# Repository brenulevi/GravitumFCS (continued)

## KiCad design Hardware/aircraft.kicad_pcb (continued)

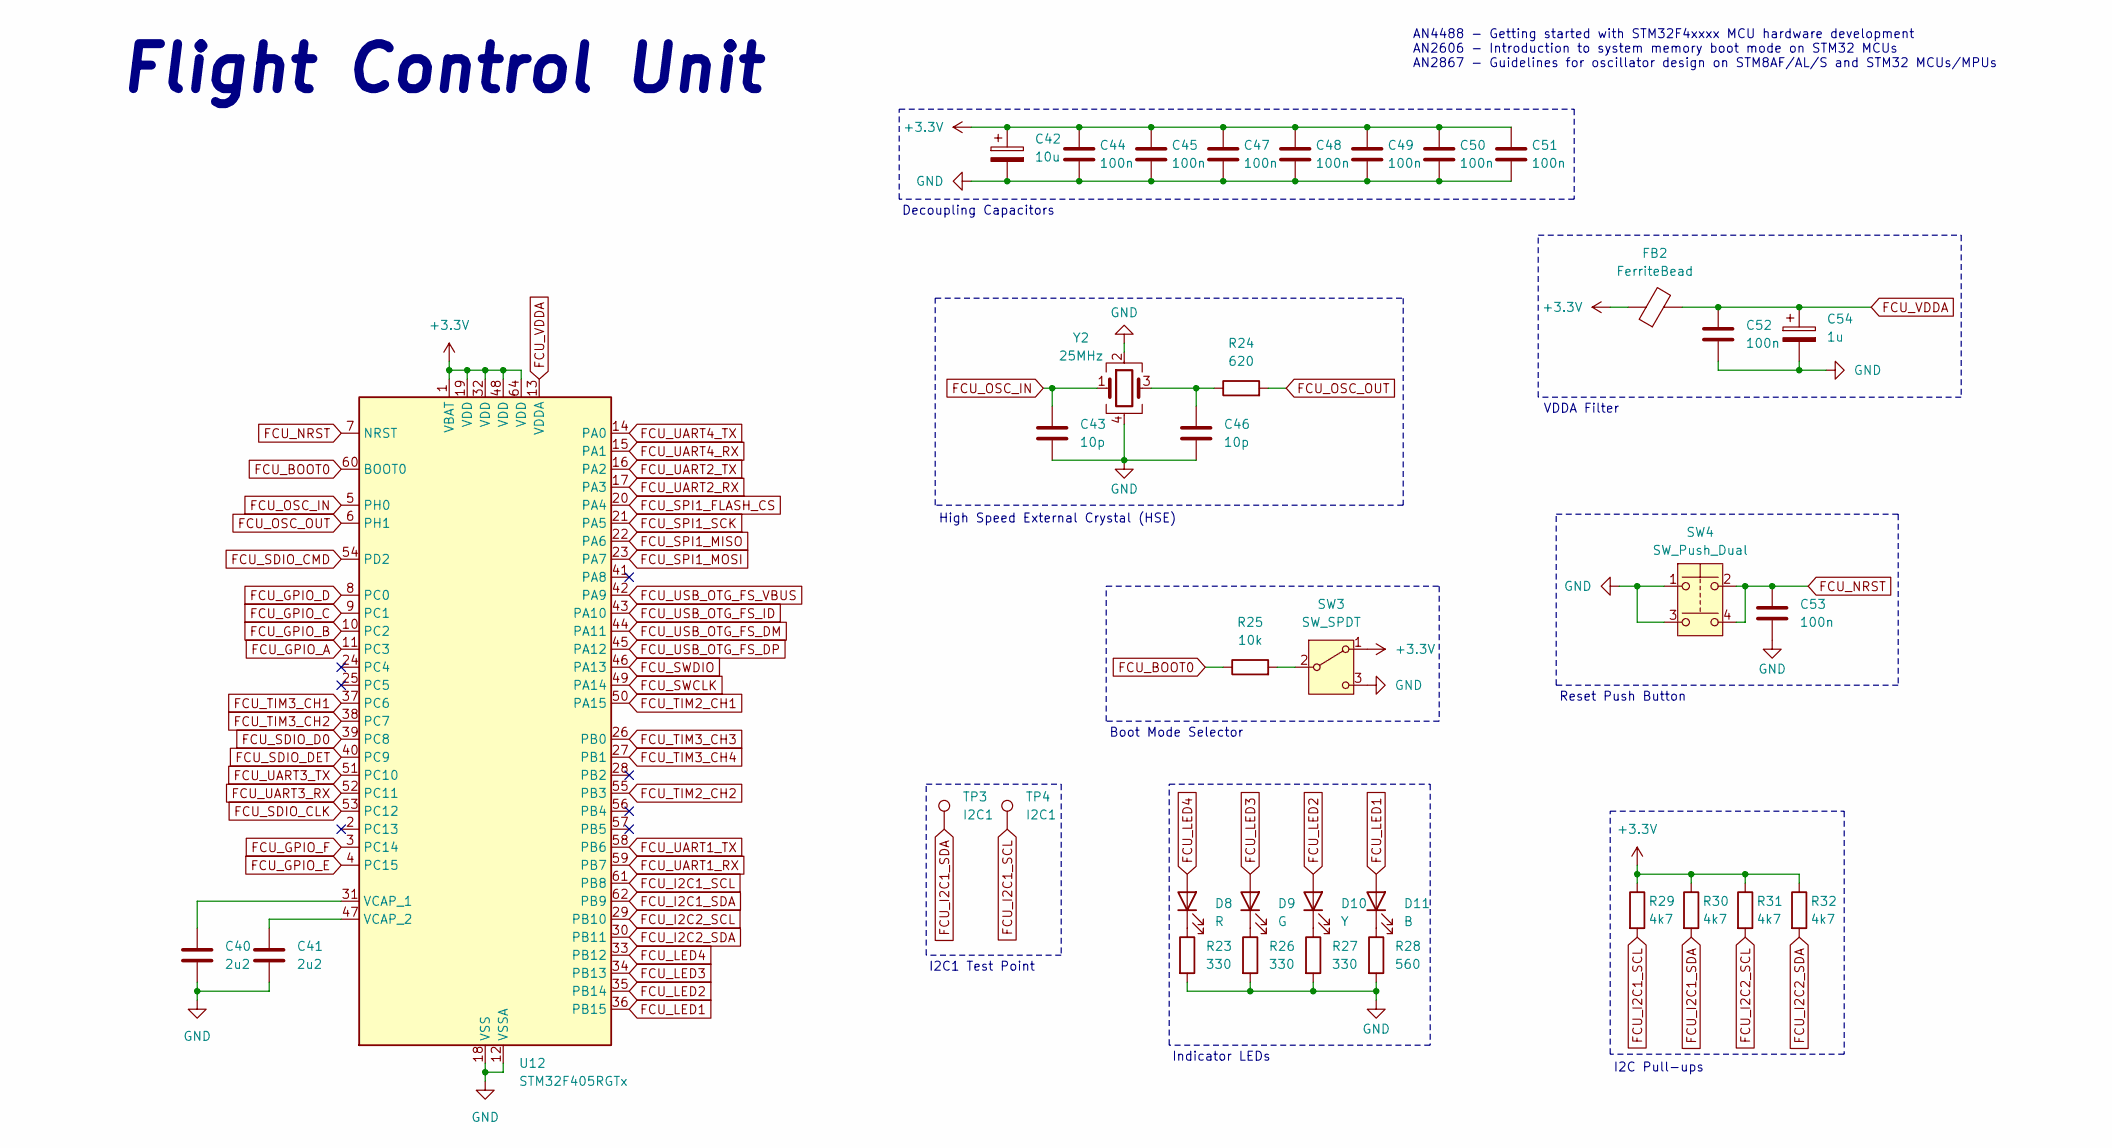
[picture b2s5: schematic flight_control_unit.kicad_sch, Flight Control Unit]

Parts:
C40, C41: 2u2; C_0402_1005Metric; MPN CL10B225KP8NNNC
C42: 10u; C_0603_1608Metric; MPN TAJA106K010TNJ
C43, C46: 10p; C_0402_1005Metric; MPN 885012005007
C44, C45, C47, C48, C49, C50, C51, C52: 100n; C_0402_1005Metric; MPN CL05B104KP5NNNC
C53: 100n; C_0402_1005Metric; MPN C0603C104K8RACTU
C54: 1u; CP_EIA-1608-08_AVX-J; MPN T491A105K010AT
D8: R; LED_0402_1005Metric; MPN LTST-C171KRKT
D9: G; LED_0402_1005Metric; MPN LTST-C170GKT
D10: Y; LED_0402_1005Metric; MPN LTST-C171YKT
D11: B; LED_0402_1005Metric; MPN LTST-C171TBKT
FB2: FerriteBead; L_0402_1005Metric; MPN HZ0805E601R-10
R23, R26, R27: 330; R_0402_1005Metric; MPN RC0603JR-07330RL
R24: 620; R_0402_1005Metric; MPN RC0603FR-07620RL
R25: 10k; R_0402_1005Metric; MPN RC0603FR-0710KL
R28: 560; R_0402_1005Metric; MPN RMCF0603FT560R
R29, R30, R31, R32: 4k7; R_0402_1005Metric; MPN ERJ-3EKF4701V
SW3: SW_SPDT; SW_SPDT_PCM12; MPN PCM12SMTR
SW4: SW_Push_Dual; SW4_PTS815 SJM 250 SMTR LFS_CNK; MPN PTS815SJM250SMTRLFS
TP3, TP4: I2C1; TestPoint_Pad_D1.0mm
U12: STM32F405RGTx; LQFP-64_10x10mm_P0.5mm; MPN STM32F405RGT6
Y2: 25MHz; Crystal_SMD_Abracon_ABM8G-4Pin_3.2x2.5mm; MPN ABM8G-25.000MHZ-B4Y-T3

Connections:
+3.3V: C42.1, C44.1, C45.1, C47.1, C48.1, C49.1, C50.1, C51.1, FB2.1, R29.1, R30.1, R31.1, R32.1, SW3.1 (A), U12.1 (VBAT), U12.19 (VDD), U12.32 (VDD), U12.48 (VDD), U12.64 (VDD); also elsewhere on the board
FCU_BOOT0: R25.1, U12.60 (BOOT0)
FCU_GPIO_A: U12.11 (PC3); also elsewhere on the board
FCU_GPIO_B: U12.10 (PC2); also elsewhere on the board
FCU_GPIO_C: U12.9 (PC1); also elsewhere on the board
FCU_GPIO_D: U12.8 (PC0); also elsewhere on the board
FCU_GPIO_E: U12.4 (PC15); also elsewhere on the board
FCU_GPIO_F: U12.3 (PC14); also elsewhere on the board
FCU_I2C1_SCL: R29.2, TP4.1, U12.61 (PB8); also elsewhere on the board
FCU_I2C1_SDA: R30.2, TP3.1, U12.62 (PB9); also elsewhere on the board
FCU_I2C2_SCL: R31.2, U12.29 (PB10); also elsewhere on the board
FCU_I2C2_SDA: R32.2, U12.30 (PB11); also elsewhere on the board
FCU_LED1: D11.2 (A), U12.36 (PB15)
FCU_LED2: D10.2 (A), U12.35 (PB14)
FCU_LED3: D9.2 (A), U12.34 (PB13)
FCU_LED4: D8.2 (A), U12.33 (PB12)
FCU_NRST: C53.1, SW4.2, SW4.4, U12.7 (NRST); also elsewhere on the board
FCU_OSC_IN: C43.1, U12.5 (PH0), Y2.1
FCU_OSC_OUT: R24.2, U12.6 (PH1)
FCU_SDIO_CLK: U12.53 (PC12); also elsewhere on the board
FCU_SDIO_CMD: U12.54 (PD2); also elsewhere on the board
FCU_SDIO_D0: U12.39 (PC8); also elsewhere on the board
FCU_SDIO_DET: U12.40 (PC9); also elsewhere on the board
FCU_SPI1_FLASH_CS: U12.20 (PA4); also elsewhere on the board
FCU_SPI1_MISO: U12.22 (PA6); also elsewhere on the board
FCU_SPI1_MOSI: U12.23 (PA7); also elsewhere on the board
FCU_SPI1_SCK: U12.21 (PA5); also elsewhere on the board
FCU_SWCLK: U12.49 (PA14); also elsewhere on the board
FCU_SWDIO: U12.46 (PA13); also elsewhere on the board
FCU_TIM2_CH1: U12.50 (PA15); also elsewhere on the board
FCU_TIM2_CH2: U12.55 (PB3); also elsewhere on the board
FCU_TIM3_CH1: U12.37 (PC6); also elsewhere on the board
FCU_TIM3_CH2: U12.38 (PC7); also elsewhere on the board
FCU_TIM3_CH3: U12.26 (PB0); also elsewhere on the board
FCU_TIM3_CH4: U12.27 (PB1); also elsewhere on the board
FCU_UART1_RX: U12.59 (PB7); also elsewhere on the board
FCU_UART1_TX: U12.58 (PB6); also elsewhere on the board
FCU_UART2_RX: U12.17 (PA3); also elsewhere on the board
FCU_UART2_TX: U12.16 (PA2); also elsewhere on the board
FCU_UART3_RX: U12.52 (PC11); also elsewhere on the board
FCU_UART3_TX: U12.51 (PC10); also elsewhere on the board
FCU_UART4_RX: U12.15 (PA1); also elsewhere on the board
FCU_UART4_TX: U12.14 (PA0); also elsewhere on the board
FCU_USB_OTG_FS_ID: U12.43 (PA10); also elsewhere on the board
FCU_USB_OTG_FS_VBUS: U12.42 (PA9); also elsewhere on the board
FCU_VDDA: C52.1, C54.1, FB2.2, U12.13 (VDDA)
GND: C40.2, C41.2, C42.2, C43.2, C44.2, C45.2, C46.2, C47.2, C48.2, C49.2, C50.2, C51.2, C52.2, C53.2, C54.2, R23.2, R26.2, R27.2, R28.2, SW3.3 (C), SW4.1, SW4.3, U12.12 (VSSA), U12.18 (VSS), U12.63 (VSS), Y2.2, Y2.4; also elsewhere on the board
unnamed: C46.1, R24.1, Y2.3
unnamed: D8.1 (K), R23.1
unnamed: D9.1 (K), R26.1
unnamed: D10.1 (K), R27.1
unnamed: D11.1 (K), R28.1
unnamed: R25.2, SW3.2 (B)
unnamed: C40.1, U12.31 (VCAP_1)
unnamed: C41.1, U12.47 (VCAP_2)

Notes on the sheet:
Reset Push Button
VDDA Filter
Decoupling Capacitors
I2C Pull-ups
Flight Control Unit
AN4488 - Getting started with STM32F4xxxx MCU hardware development AN2606 - Introduction to system memory boot mode on STM32 MCUs AN2867 - Guidelines for oscillator design on STM8AF/AL/S and STM32 MCUs/MPUs
Indicator LEDs
Boot Mode Selector
High Speed External Crystal (HSE)
I2C1 Test Point

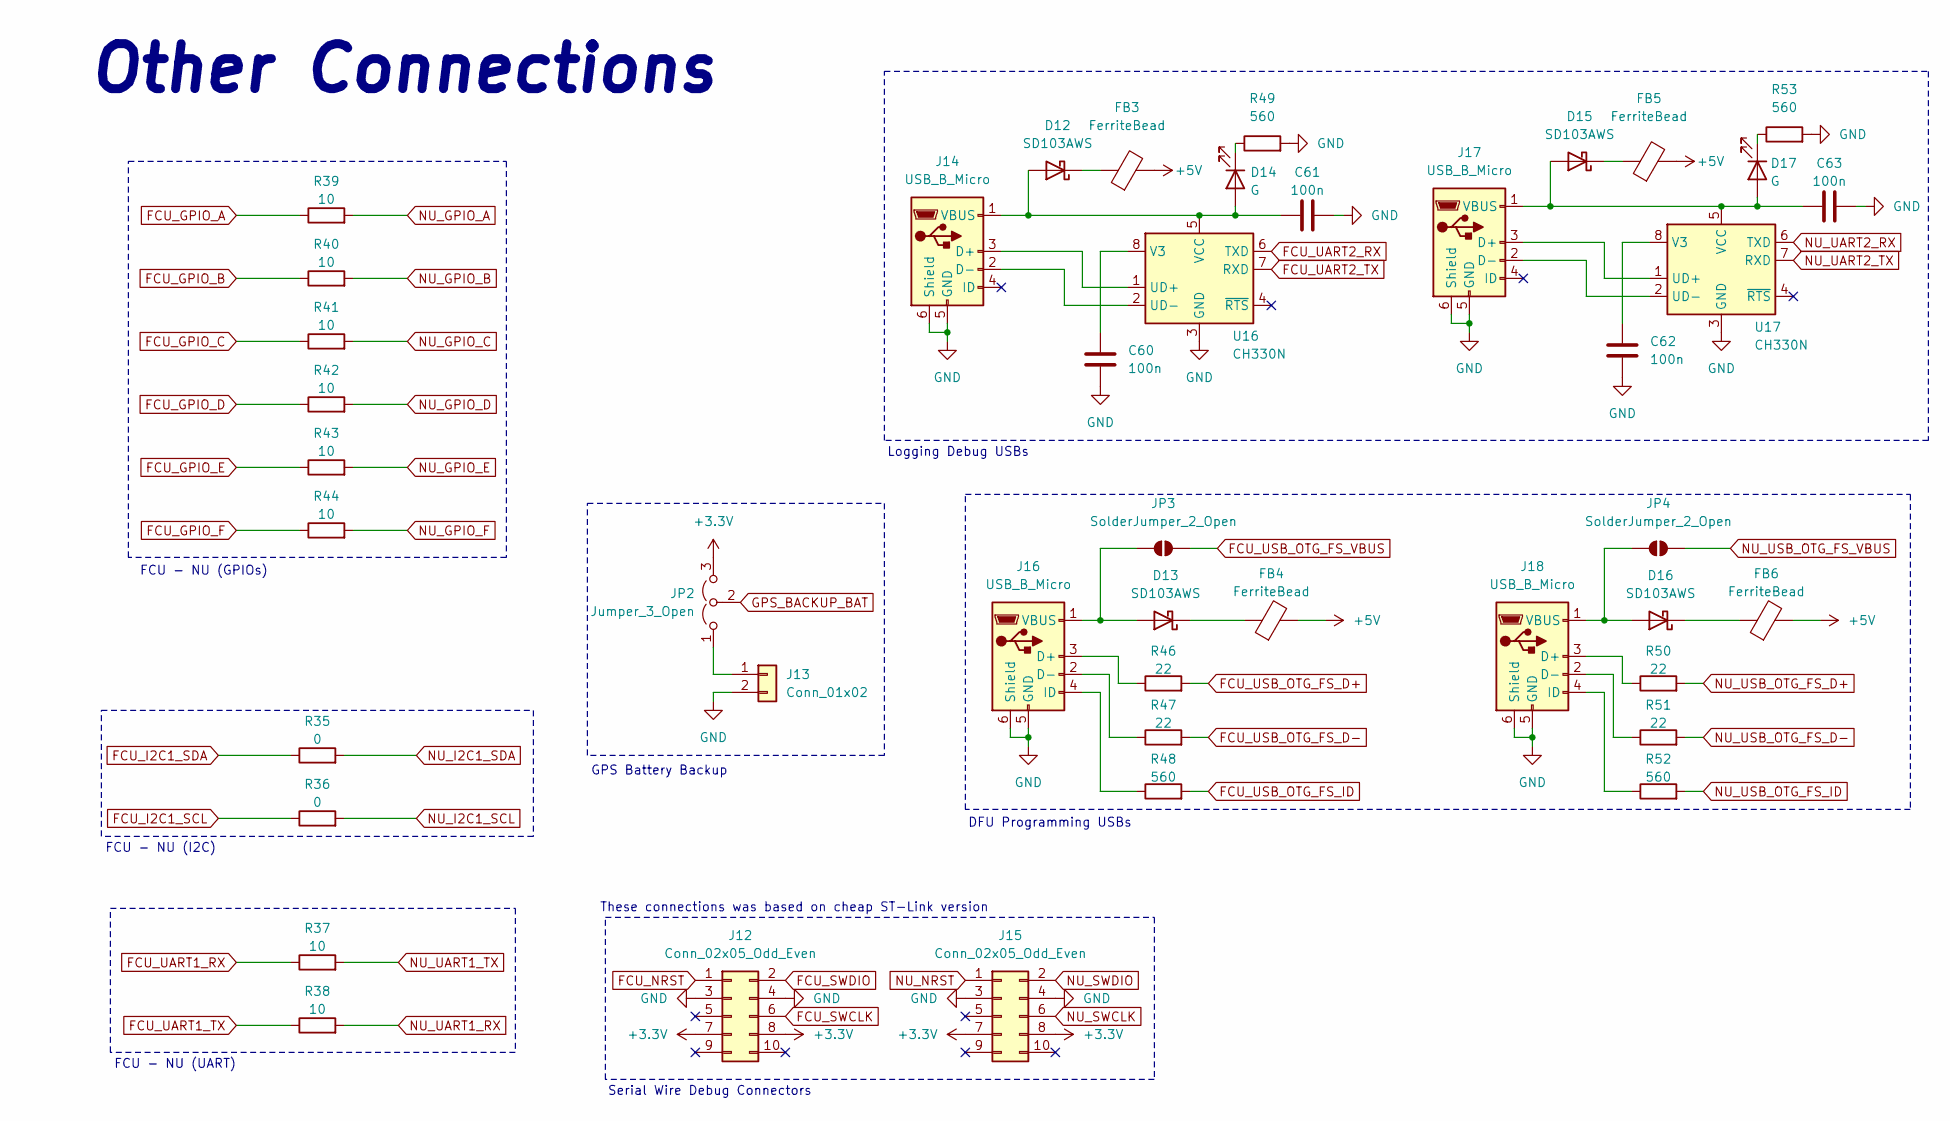
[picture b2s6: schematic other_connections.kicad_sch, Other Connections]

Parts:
C60, C62: 100n; C_0402_1005Metric; MPN C0603C104K8RACTU
C61, C63: 100n; C_0603_1608Metric; MPN C0603C104K8RACTU
D12, D13, D15, D16: SD103AWS; D_SOD-323_HandSoldering; MPN SD103AWS
D14, D17: G; LED_0402_1005Metric; MPN LTST-S270KGKT
FB3, FB4, FB5, FB6: FerriteBead; L_0603_1608Metric; MPN HZ0805E601R-10
J12, J15: Conn_02x05_Odd_Even; JST_PHD_B10B-PHDSS_2x05_P2.00mm_Vertical; MPN B10B-PHDSS
J13: Conn_01x02; JST_PH_S2B-PH-K_1x02_P2.00mm_Horizontal; MPN S2B-PH-K-S
J14, J16, J17, J18: USB_B_Micro; USB_Micro-B_Molex_47346-0001; MPN 0473461001
JP2: Jumper_3_Open; SolderJumper-3_P1.3mm_Open_RoundedPad1.0x1.5mm_NumberLabels
JP3, JP4: SolderJumper_2_Open; SolderJumper-2_P1.3mm_Open_RoundedPad1.0x1.5mm
R35, R36: 0; R_0402_1005Metric; MPN RC0603JR-070RL
R37, R38, R39, R40, R41, R42, R43, R44: 10; R_0402_1005Metric; MPN RMCF0603FT10R0
R46, R47, R50, R51: 22; R_0402_1005Metric; MPN RC0603FR-0722RL
R48, R49, R52, R53: 560; R_0402_1005Metric; MPN RMCF0603FT560R
U16, U17: CH330N; SOIC-8_3.9x4.9mm_P1.27mm; MPN CH330N

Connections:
+3.3V: J12.7, J12.8, J15.7, J15.8, JP2.3 (B); also elsewhere on the board
+5V: FB3.2, FB4.2, FB5.2, FB6.2; also elsewhere on the board
FCU_GPIO_A: R39.1; also elsewhere on the board
FCU_GPIO_B: R40.1; also elsewhere on the board
FCU_GPIO_C: R41.1; also elsewhere on the board
FCU_GPIO_D: R42.1; also elsewhere on the board
FCU_GPIO_E: R43.1; also elsewhere on the board
FCU_GPIO_F: R44.1; also elsewhere on the board
FCU_I2C1_SCL: R36.1; also elsewhere on the board
FCU_I2C1_SDA: R35.1; also elsewhere on the board
FCU_NRST: J12.1; also elsewhere on the board
FCU_SWCLK: J12.6; also elsewhere on the board
FCU_SWDIO: J12.2; also elsewhere on the board
FCU_UART1_RX: R37.1; also elsewhere on the board
FCU_UART1_TX: R38.1; also elsewhere on the board
FCU_UART2_RX: U16.6 (TXD); also elsewhere on the board
FCU_UART2_TX: U16.7 (RXD); also elsewhere on the board
FCU_USB_OTG_FS_ID: R48.2; also elsewhere on the board
FCU_USB_OTG_FS_VBUS: JP3.2 (B); also elsewhere on the board
GND: C60.2, C61.2, C62.2, C63.2, J12.3, J12.4, J13.2, J14.5 (GND), J14.6 (Shield), J15.3, J15.4, J16.5 (GND), J16.6 (Shield), J17.5 (GND), J17.6 (Shield), J18.5 (GND), J18.6 (Shield), R49.2, R53.2, U16.3 (GND), U17.3 (GND); also elsewhere on the board
GPS_BACKUP_BAT: JP2.2 (C); also elsewhere on the board
NU_GPIO_A: R39.2; also elsewhere on the board
NU_GPIO_B: R40.2; also elsewhere on the board
NU_GPIO_C: R41.2; also elsewhere on the board
NU_GPIO_D: R42.2; also elsewhere on the board
NU_GPIO_E: R43.2; also elsewhere on the board
NU_GPIO_F: R44.2; also elsewhere on the board
NU_I2C1_SCL: R36.2; also elsewhere on the board
NU_I2C1_SDA: R35.2; also elsewhere on the board
NU_NRST: J15.1; also elsewhere on the board
NU_SWCLK: J15.6; also elsewhere on the board
NU_SWDIO: J15.2; also elsewhere on the board
NU_UART1_RX: R38.2; also elsewhere on the board
NU_UART1_TX: R37.2; also elsewhere on the board
NU_UART2_RX: U17.6 (TXD); also elsewhere on the board
NU_UART2_TX: U17.7 (RXD); also elsewhere on the board
NU_USB_OTG_FS_D+: R50.2; also elsewhere on the board
NU_USB_OTG_FS_D-: R51.2; also elsewhere on the board
NU_USB_OTG_FS_ID: R52.2; also elsewhere on the board
NU_USB_OTG_FS_VBUS: JP4.2 (B); also elsewhere on the board
unnamed: C61.1, D12.2 (A), D14.2 (A), J14.1 (VBUS), U16.5 (VCC)
unnamed: D12.1 (K), FB3.1
unnamed: D13.2 (A), J16.1 (VBUS), JP3.1 (A)
unnamed: D13.1 (K), FB4.1
unnamed: D14.1 (K), R49.1
unnamed: C63.1, D15.2 (A), D17.2 (A), J17.1 (VBUS), U17.5 (VCC)
unnamed: D15.1 (K), FB5.1
unnamed: D16.2 (A), J18.1 (VBUS), JP4.1 (A)
unnamed: D16.1 (K), FB6.1
unnamed: D17.1 (K), R53.1
unnamed: J13.1, JP2.1 (A)
unnamed: J14.3 (D+), U16.1 (UD+)
unnamed: J14.2 (D-), U16.2 (UD-)
unnamed: J16.3 (D+), R46.1
unnamed: J16.2 (D-), R47.1
unnamed: J16.4 (ID), R48.1
unnamed: J17.3 (D+), U17.1 (UD+)
unnamed: J17.2 (D-), U17.2 (UD-)
unnamed: J18.3 (D+), R50.1
unnamed: J18.2 (D-), R51.1
unnamed: J18.4 (ID), R52.1
unnamed: C60.1, U16.8 (V3)
unnamed: C62.1, U17.8 (V3)

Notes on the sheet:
FCU - NU (GPIOs)
Serial Wire Debug Connectors
Other Connections
DFU Programming USBs
GPS Battery Backup
FCU - NU (I2C)
These connections was based on cheap ST-Link version
Logging Debug USBs
FCU - NU (UART)

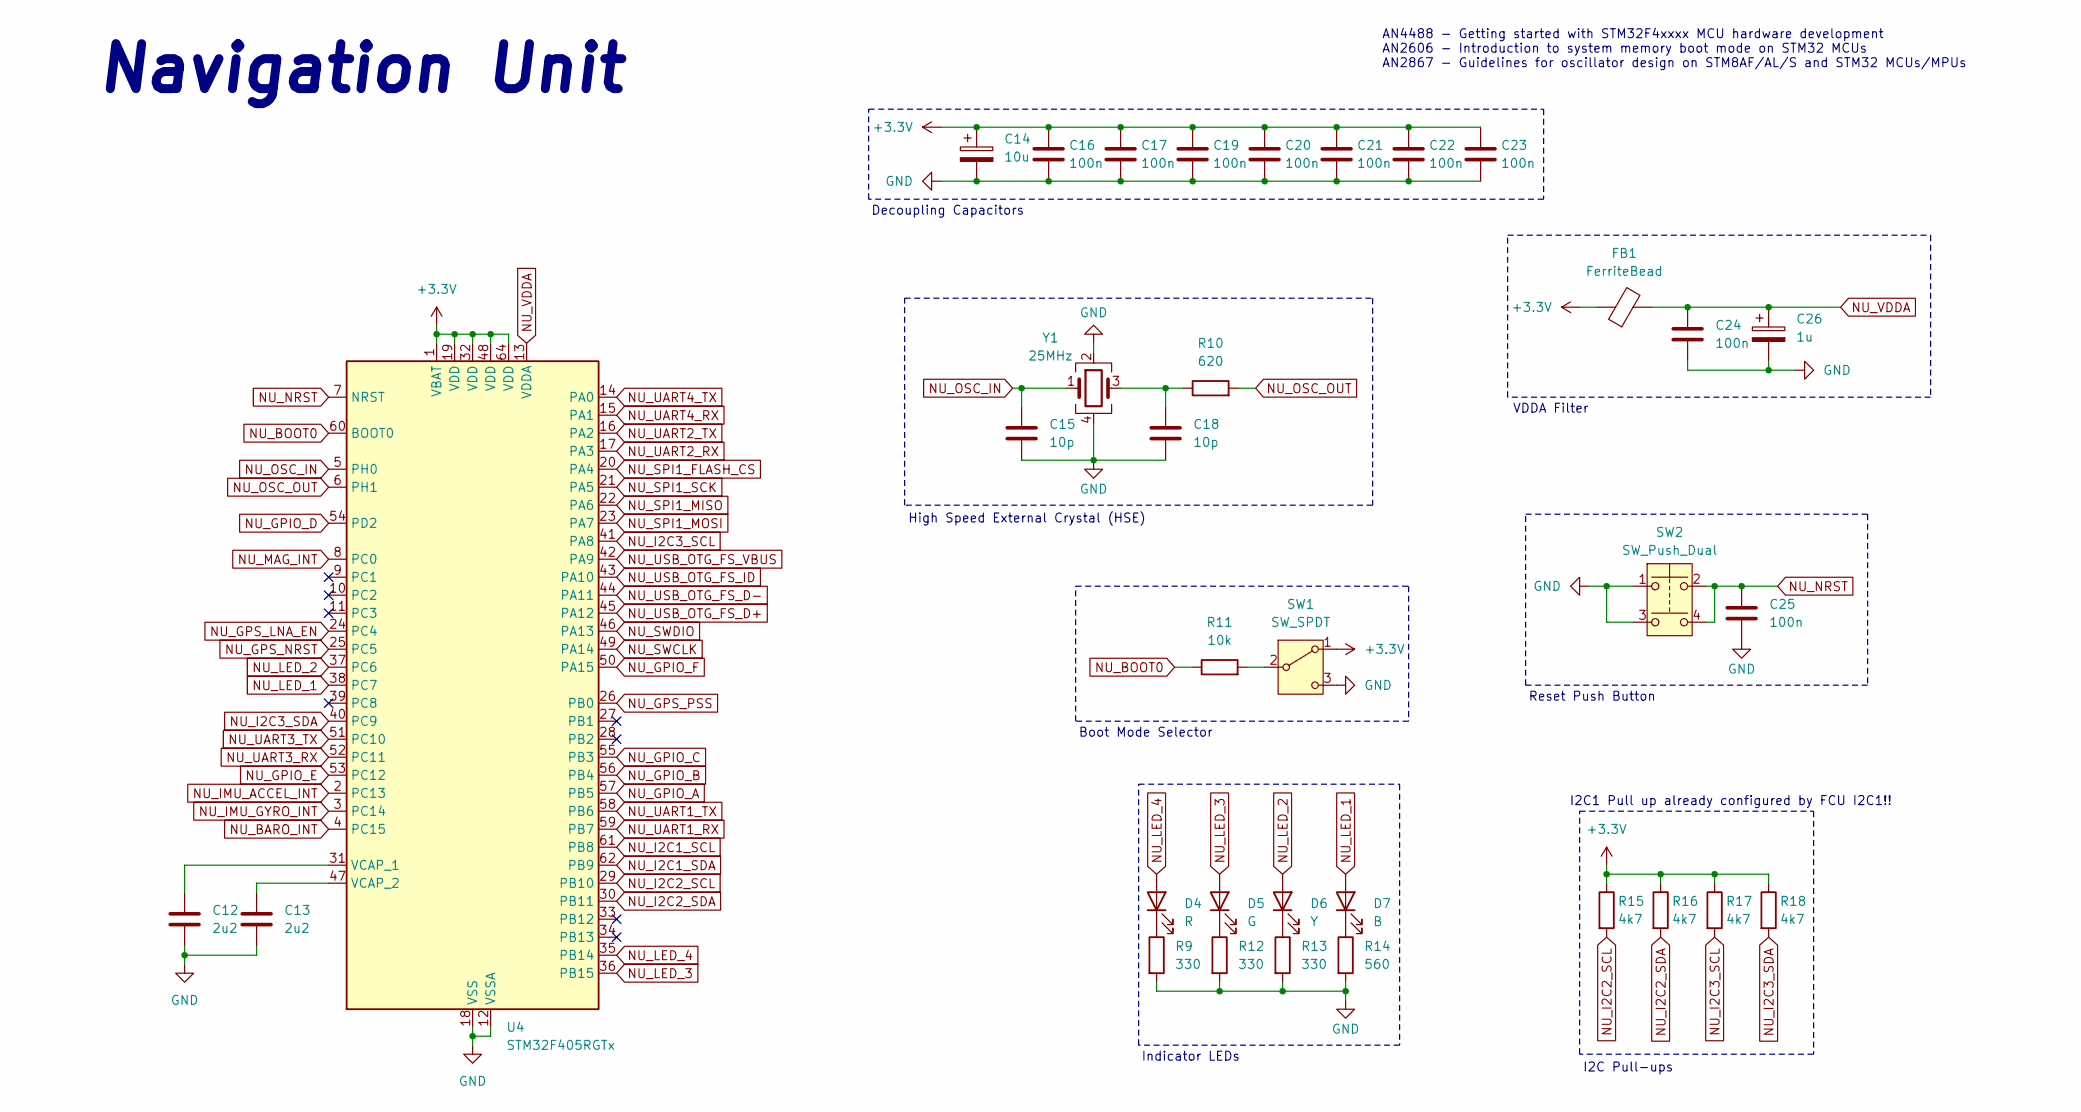
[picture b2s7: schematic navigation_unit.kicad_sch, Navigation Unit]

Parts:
C12, C13: 2u2; C_0402_1005Metric; MPN CL10B225KP8NNNC
C14: 10u; C_0603_1608Metric; MPN TAJA106K010TNJ
C15, C18: 10p; C_0402_1005Metric; MPN 885012005007
C16, C17, C19, C20, C21, C22, C23, C24: 100n; C_0402_1005Metric; MPN CL05B104KP5NNNC
C25: 100n; C_0402_1005Metric; MPN C0603C104K8RACTU
C26: 1u; CP_EIA-1608-08_AVX-J; MPN T491A105K010AT
D4: R; LED_0402_1005Metric; MPN LTST-C171KRKT
D5: G; LED_0402_1005Metric; MPN LTST-C170GKT
D6: Y; LED_0402_1005Metric; MPN LTST-C171YKT
D7: B; LED_0402_1005Metric; MPN LTST-C171TBKT
FB1: FerriteBead; L_0402_1005Metric; MPN HZ0805E601R-10
R9, R12, R13: 330; R_0402_1005Metric; MPN RC0603JR-07330RL
R10: 620; R_0402_1005Metric; MPN RC0603FR-07620RL
R11: 10k; R_0402_1005Metric; MPN RC0603FR-0710KL
R14: 560; R_0402_1005Metric; MPN RMCF0603FT560R
R15, R16, R17, R18: 4k7; R_0402_1005Metric; MPN ERJ-3EKF4701V
SW1: SW_SPDT; SW_SPDT_PCM12; MPN PCM12SMTR
SW2: SW_Push_Dual; SW4_PTS815 SJM 250 SMTR LFS_CNK; MPN PTS815SJM250SMTRLFS
U4: STM32F405RGTx; LQFP-64_10x10mm_P0.5mm; MPN STM32F405RGT6
Y1: 25MHz; Crystal_SMD_Abracon_ABM8G-4Pin_3.2x2.5mm; MPN ABM8G-25.000MHZ-B4Y-T3

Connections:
+3.3V: C14.1, C16.1, C17.1, C19.1, C20.1, C21.1, C22.1, C23.1, FB1.1, R15.1, R16.1, R17.1, R18.1, SW1.1 (A), U4.1 (VBAT), U4.19 (VDD), U4.32 (VDD), U4.48 (VDD), U4.64 (VDD); also elsewhere on the board
GND: C12.2, C13.2, C14.2, C15.2, C16.2, C17.2, C18.2, C19.2, C20.2, C21.2, C22.2, C23.2, C24.2, C25.2, C26.2, R9.2, R12.2, R13.2, R14.2, SW1.3 (C), SW2.1, SW2.3, U4.12 (VSSA), U4.18 (VSS), U4.63 (VSS), Y1.2, Y1.4; also elsewhere on the board
NU_BARO_INT: U4.4 (PC15); also elsewhere on the board
NU_BOOT0: R11.1, U4.60 (BOOT0)
NU_GPIO_A: U4.57 (PB5); also elsewhere on the board
NU_GPIO_B: U4.56 (PB4); also elsewhere on the board
NU_GPIO_C: U4.55 (PB3); also elsewhere on the board
NU_GPIO_D: U4.54 (PD2); also elsewhere on the board
NU_GPIO_E: U4.53 (PC12); also elsewhere on the board
NU_GPIO_F: U4.50 (PA15); also elsewhere on the board
NU_GPS_LNA_EN: U4.24 (PC4); also elsewhere on the board
NU_GPS_NRST: U4.25 (PC5); also elsewhere on the board
NU_GPS_PSS: U4.26 (PB0); also elsewhere on the board
NU_I2C1_SCL: U4.61 (PB8); also elsewhere on the board
NU_I2C1_SDA: U4.62 (PB9); also elsewhere on the board
NU_I2C2_SCL: R15.2, U4.29 (PB10); also elsewhere on the board
NU_I2C2_SDA: R16.2, U4.30 (PB11); also elsewhere on the board
NU_I2C3_SCL: R17.2, U4.41 (PA8); also elsewhere on the board
NU_I2C3_SDA: R18.2, U4.40 (PC9); also elsewhere on the board
NU_IMU_ACCEL_INT: U4.2 (PC13); also elsewhere on the board
NU_IMU_GYRO_INT: U4.3 (PC14); also elsewhere on the board
NU_LED_1: D7.2 (A), U4.38 (PC7)
NU_LED_2: D6.2 (A), U4.37 (PC6)
NU_LED_3: D5.2 (A), U4.36 (PB15)
NU_LED_4: D4.2 (A), U4.35 (PB14)
NU_MAG_INT: U4.8 (PC0); also elsewhere on the board
NU_NRST: C25.1, SW2.2, SW2.4, U4.7 (NRST); also elsewhere on the board
NU_OSC_IN: C15.1, U4.5 (PH0), Y1.1
NU_OSC_OUT: R10.2, U4.6 (PH1)
NU_SPI1_FLASH_CS: U4.20 (PA4); also elsewhere on the board
NU_SPI1_MISO: U4.22 (PA6); also elsewhere on the board
NU_SPI1_MOSI: U4.23 (PA7); also elsewhere on the board
NU_SPI1_SCK: U4.21 (PA5); also elsewhere on the board
NU_SWCLK: U4.49 (PA14); also elsewhere on the board
NU_SWDIO: U4.46 (PA13); also elsewhere on the board
NU_UART1_RX: U4.59 (PB7); also elsewhere on the board
NU_UART1_TX: U4.58 (PB6); also elsewhere on the board
NU_UART2_RX: U4.17 (PA3); also elsewhere on the board
NU_UART2_TX: U4.16 (PA2); also elsewhere on the board
NU_UART3_RX: U4.52 (PC11); also elsewhere on the board
NU_UART3_TX: U4.51 (PC10); also elsewhere on the board
NU_UART4_RX: U4.15 (PA1); also elsewhere on the board
NU_UART4_TX: U4.14 (PA0); also elsewhere on the board
NU_USB_OTG_FS_D+: U4.45 (PA12); also elsewhere on the board
NU_USB_OTG_FS_D-: U4.44 (PA11); also elsewhere on the board
NU_USB_OTG_FS_ID: U4.43 (PA10); also elsewhere on the board
NU_USB_OTG_FS_VBUS: U4.42 (PA9); also elsewhere on the board
NU_VDDA: C24.1, C26.1, FB1.2, U4.13 (VDDA)
unnamed: C18.1, R10.1, Y1.3
unnamed: D4.1 (K), R9.1
unnamed: D5.1 (K), R12.1
unnamed: D6.1 (K), R13.1
unnamed: D7.1 (K), R14.1
unnamed: R11.2, SW1.2 (B)
unnamed: C12.1, U4.31 (VCAP_1)
unnamed: C13.1, U4.47 (VCAP_2)

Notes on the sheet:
Decoupling Capacitors
I2C Pull-ups
Indicator LEDs
I2C1 Pull up already configured by FCU I2C1!!
Reset Push Button
Boot Mode Selector
VDDA Filter
AN4488 - Getting started with STM32F4xxxx MCU hardware development AN2606 - Introduction to system memory boot mode on STM32 MCUs AN2867 - Guidelines for oscillator design on STM8AF/AL/S and STM32 MCUs/MPUs
Navigation Unit
High Speed External Crystal (HSE)

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
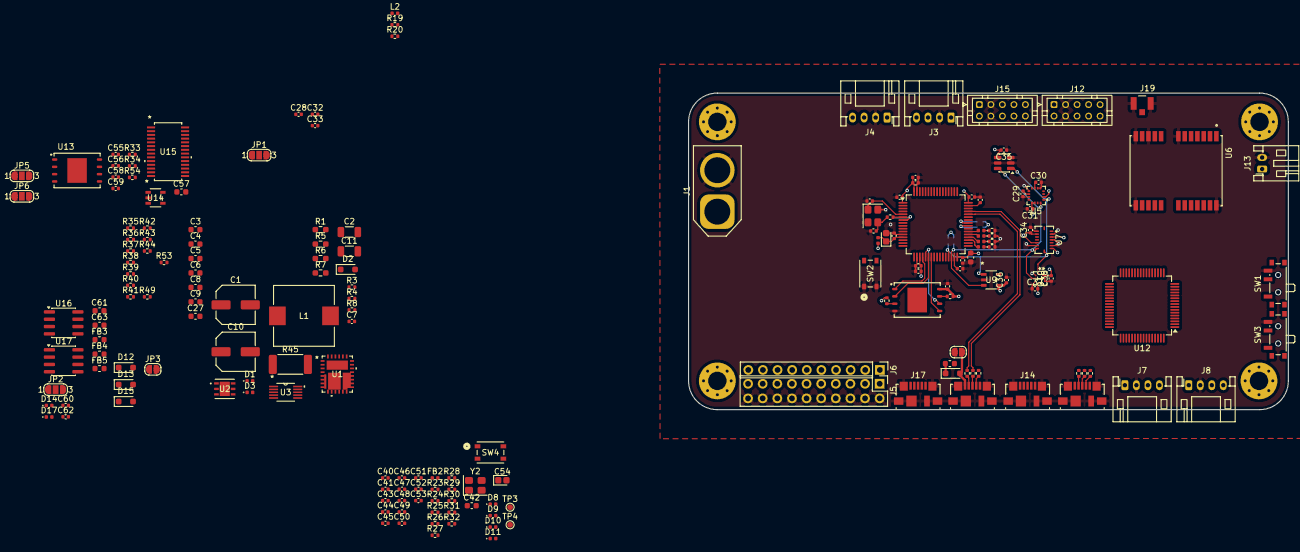
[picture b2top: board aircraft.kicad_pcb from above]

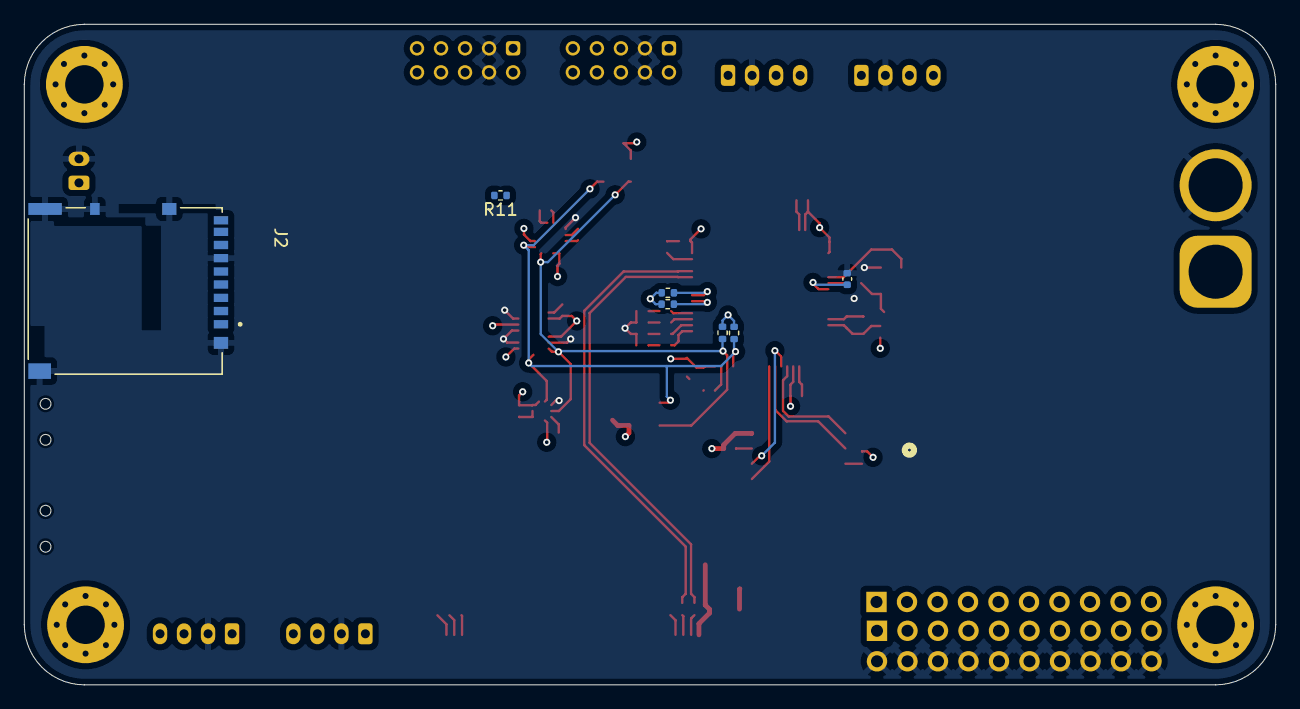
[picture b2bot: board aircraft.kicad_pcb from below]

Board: 4 copper layers, 104.2 x 55.0 mm, 188 parts (7 on the bottom side), 163 nets.

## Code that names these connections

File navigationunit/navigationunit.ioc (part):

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Mcu.Name=STM32F405RGTx
Mcu.Package=LQFP64
Mcu.UserName=STM32F405RGTx
PA0-WKUP.Mode=Asynchronous
PA0-WKUP.Signal=UART4_TX
PA1.Mode=Asynchronous
PA1.Signal=UART4_RX
PA10.Mode=OTG/Dual_Role_Device
PA10.Signal=USB_OTG_FS_ID
PA11.Mode=OTG/Dual_Role_Device
PA11.Signal=USB_OTG_FS_DM
PA12.Mode=OTG/Dual_Role_Device
PA12.Signal=USB_OTG_FS_DP
PA13.Mode=Serial_Wire
PA13.Signal=SYS_JTMS-SWDIO
PA14.Mode=Serial_Wire
PA14.Signal=SYS_JTCK-SWCLK
PA2.Mode=Asynchronous
PA2.Signal=USART2_TX
PA3.Mode=Asynchronous
PA3.Signal=USART2_RX
PA4.GPIOParameters=GPIO_Label
PA4.GPIO_Label=NU_SPI1_CS_GYRO
PA4.Signal=GPIO_Output
PA5.Mode=Full_Duplex_Master
PA5.Signal=SPI1_SCK
PA6.Mode=Full_Duplex_Master
PA6.Signal=SPI1_MISO
PA7.Mode=Full_Duplex_Master
PA7.Signal=SPI1_MOSI
PA8.GPIOParameters=GPIO_Label
PA8.GPIO_Label=NU_GPIO_A
PA8.Signal=GPIO_Input
PA9.Mode=Activate_VBUS
PA9.Signal=USB_OTG_FS_VBUS
PB0.GPIOParameters=GPIO_Label
PB0.GPIO_Label=NU_GNSS_PSS
PB0.Signal=GPIO_Input
PB1.GPIOParameters=GPIO_Label
PB1.GPIO_Label=NU_GNSS_LNA_EN
PB1.Signal=GPIO_Input
PB10.Mode=I2C
PB10.Signal=I2C2_SCL
PB11.Mode=I2C
PB11.Signal=I2C2_SDA
PB13.GPIOParameters=GPIO_Label
PB13.GPIO_Label=NU_GPIO_H
PB13.Signal=GPIO_Output
PB14.GPIOParameters=GPIO_Label
PB14.GPIO_Label=NU_GPIO_G
PB14.Signal=GPIO_Input
PB15.GPIOParameters=GPIO_Label
PB15.GPIO_Label=NU_GPIO_F
PB15.Signal=GPIO_Output
PB2.GPIOParameters=GPIO_Label
PB2.GPIO_Label=NU_BOOT1
PB2.Signal=GPIO_Input
PB3.GPIOParameters=GPIO_Label
PB3.GPIO_Label=NU_LED_C
PB3.Signal=GPIO_Output
PB4.GPIOParameters=GPIO_Label
PB4.GPIO_Label=NU_LED_B
PB4.Signal=GPIO_Output
PB5.GPIOParameters=GPIO_Label
PB5.GPIO_Label=NU_LED_A
PB5.Signal=GPIO_Output
PB6.Mode=Asynchronous
PB6.Signal=USART1_TX
PB7.Mode=Asynchronous
PB7.Signal=USART1_RX
PB8.Mode=I2C
PB8.Signal=I2C1_SCL
PB9.Mode=I2C
PB9.Signal=I2C1_SDA
PC0.GPIOParameters=GPIO_Label
PC0.GPIO_Label=NU_GYRO_INT
PC0.Signal=GPIO_Input
PC1.GPIOParameters=GPIO_Label
PC1.GPIO_Label=NU_ACCEL_INT
PC1.Signal=GPIO_Input
PC10.Mode=Asynchronous
PC10.Signal=USART3_TX
PC11.Mode=Asynchronous
PC11.Signal=USART3_RX
PC12.GPIOParameters=GPIO_Label
PC12.GPIO_Label=NU_LED_E
PC12.Signal=GPIO_Output
PC2.GPIOParameters=GPIO_Label
PC2.GPIO_Label=NU_BARO_INT
PC2.Signal=GPIO_Input
PC3.GPIOParameters=GPIO_Label
PC3.GPIO_Label=NU_MAG_INT
PC3.Signal=GPIO_Input
PC4.GPIOParameters=GPIO_Label
PC4.GPIO_Label=NU_SPI1_CS_ACCEL
PC4.Signal=GPIO_Output
PC5.GPIOParameters=GPIO_Label
PC5.GPIO_Label=NU_GNSS_NRST
PC5.Signal=GPIO_Output
PC6.GPIOParameters=GPIO_Label
PC6.GPIO_Label=NU_GPIO_E
PC6.Signal=GPIO_Input
PC7.GPIOParameters=GPIO_Label
PC7.GPIO_Label=NU_GPIO_D
PC7.Signal=GPIO_Output
PC8.GPIOParameters=GPIO_Label
PC8.GPIO_Label=NU_GPIO_C
PC8.Signal=GPIO_Input
PC9.GPIOParameters=GPIO_Label
PC9.GPIO_Label=NU_GPIO_B
PC9.Signal=GPIO_Output
PD2.GPIOParameters=GPIO_Label
PD2.GPIO_Label=NU_LED_D
PD2.Signal=GPIO_Output
PH0-OSC_IN.Mode=HSE-External-Oscillator
PH0-OSC_IN.Signal=RCC_OSC_IN
PH1-OSC_OUT.Mode=HSE-External-Oscillator
PH1-OSC_OUT.Signal=RCC_OSC_OUT
RCC.HSE_VALUE=25000000
RCC.SYSCLKFreq_VALUE=25000000
RCC.SYSCLKSource=RCC_SYSCLKSOURCE_HSE
board=custom

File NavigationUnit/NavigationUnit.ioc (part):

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Mcu.Name=STM32F405RGTx
Mcu.Package=LQFP64
Mcu.UserName=STM32F405RGTx
PA0-WKUP.Mode=Asynchronous
PA0-WKUP.Signal=UART4_TX
PA1.Mode=Asynchronous
PA1.Signal=UART4_RX
PA10.Mode=OTG/Dual_Role_Device
PA10.Signal=USB_OTG_FS_ID
PA11.Mode=OTG/Dual_Role_Device
PA11.Signal=USB_OTG_FS_DM
PA12.Mode=OTG/Dual_Role_Device
PA12.Signal=USB_OTG_FS_DP
PA13.Mode=Serial_Wire
PA13.Signal=SYS_JTMS-SWDIO
PA14.Mode=Serial_Wire
PA14.Signal=SYS_JTCK-SWCLK
PA15.GPIOParameters=GPIO_Label
PA15.GPIO_Label=NU_GPIO_F
PA15.Signal=GPIO_Output
PA2.Mode=Asynchronous
PA2.Signal=USART2_TX
PA3.Mode=Asynchronous
PA3.Signal=USART2_RX
PA4.GPIOParameters=GPIO_Label
PA4.GPIO_Label=NU_SPI1_CS_FLASH
PA4.Signal=GPIO_Input
PA5.Mode=Full_Duplex_Master
PA5.Signal=SPI1_SCK
PA6.Mode=Full_Duplex_Master
PA6.Signal=SPI1_MISO
PA7.Mode=Full_Duplex_Master
PA7.Signal=SPI1_MOSI
PA8.Mode=I2C
PA8.Signal=I2C3_SCL
PA9.Mode=Activate_VBUS
PA9.Signal=USB_OTG_FS_VBUS
PB0.GPIOParameters=GPIO_Label
PB0.GPIO_Label=NU_GPS_PSS
PB0.Signal=GPIO_Input
PB10.Mode=I2C
PB10.Signal=I2C2_SCL
PB11.Mode=I2C
PB11.Signal=I2C2_SDA
PB12.GPIOParameters=GPIO_Label
PB12.GPIO_Label=NU_SPI2_CS_IMU
PB12.Signal=GPIO_Input
PB13.Mode=Full_Duplex_Master
PB13.Signal=SPI2_SCK
PB14.GPIOParameters=GPIO_Label
PB14.GPIO_Label=NU_LED_4
PB14.Signal=GPIO_Output
PB15.GPIOParameters=GPIO_Label
PB15.GPIO_Label=NU_LED_3
PB15.Signal=GPIO_Output
PB3.GPIOParameters=GPIO_Label
PB3.GPIO_Label=NU_GPIO_C
PB3.Signal=GPIO_Input
PB4.GPIOParameters=GPIO_Label
PB4.GPIO_Label=NU_GPIO_B
PB4.Signal=GPIO_Output
PB5.GPIOParameters=GPIO_Label
PB5.GPIO_Label=NU_GPIO_A
PB5.Signal=GPIO_Input
PB6.Mode=Asynchronous
PB6.Signal=USART1_TX
PB7.Mode=Asynchronous
PB7.Signal=USART1_RX
PB8.Mode=I2C
PB8.Signal=I2C1_SCL
PB9.Mode=I2C
PB9.Signal=I2C1_SDA
PC0.GPIOParameters=GPIO_Label
PC0.GPIO_Label=NU_MAG_INT
PC0.Signal=GPIO_Input
PC10.Mode=Asynchronous
PC10.Signal=USART3_TX
PC11.Mode=Asynchronous
PC11.Signal=USART3_RX
PC12.GPIOParameters=GPIO_Label
PC12.GPIO_Label=NU_GPIO_E
PC12.Signal=GPIO_Output
PC13-ANTI_TAMP.GPIOParameters=GPIO_Label
PC13-ANTI_TAMP.GPIO_Label=NU_IMU_ACCEL_INT
PC13-ANTI_TAMP.Signal=GPIO_Input
PC14-OSC32_IN.GPIOParameters=GPIO_Label
PC14-OSC32_IN.GPIO_Label=NU_IMU_GYRO_INT
PC14-OSC32_IN.Signal=GPIO_Input
PC15-OSC32_OUT.GPIOParameters=GPIO_Label
PC15-OSC32_OUT.GPIO_Label=NU_BARO_INT
PC15-OSC32_OUT.Signal=GPIO_Input
PC2.Mode=Full_Duplex_Master
PC2.Signal=SPI2_MISO
PC3.Mode=Full_Duplex_Master
PC3.Signal=SPI2_MOSI
PC4.GPIOParameters=GPIO_Label
PC4.GPIO_Label=NU_GPS_LNA_EN
PC4.Signal=GPIO_Input
PC5.GPIOParameters=GPIO_Label
PC5.GPIO_Label=NU_GPS_NRST
PC5.Signal=GPIO_Output
PC6.GPIOParameters=GPIO_Label
PC6.GPIO_Label=NU_LED_2
PC6.Signal=GPIO_Output
PC7.GPIOParameters=GPIO_Label
PC7.GPIO_Label=NU_LED_1
PC7.Signal=GPIO_Output
PC9.Mode=I2C
PC9.Signal=I2C3_SDA
PD2.GPIOParameters=GPIO_Label
PD2.GPIO_Label=NU_GPIO_D
PD2.Signal=GPIO_Output
PH0-OSC_IN.Mode=HSE-External-Oscillator
PH0-OSC_IN.Signal=RCC_OSC_IN
PH1-OSC_OUT.Mode=HSE-External-Oscillator
PH1-OSC_OUT.Signal=RCC_OSC_OUT
RCC.HSE_VALUE=25000000
RCC.SYSCLKFreq_VALUE=16000000
board=custom

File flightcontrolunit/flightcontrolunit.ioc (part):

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Mcu.Name=STM32F405RGTx
Mcu.Package=LQFP64
Mcu.UserName=STM32F405RGTx
PA0-WKUP.Mode=Asynchronous
PA0-WKUP.Signal=UART4_TX
PA1.Mode=Asynchronous
PA1.Signal=UART4_RX
PA10.Mode=OTG/Dual_Role_Device
PA10.Signal=USB_OTG_FS_ID
PA11.Mode=OTG/Dual_Role_Device
PA11.Signal=USB_OTG_FS_DM
PA12.Mode=OTG/Dual_Role_Device
PA12.Signal=USB_OTG_FS_DP
PA13.Mode=Serial_Wire
PA13.Signal=SYS_JTMS-SWDIO
PA14.Mode=Serial_Wire
PA14.Signal=SYS_JTCK-SWCLK
PA2.Mode=Asynchronous
PA2.Signal=USART2_TX
PA3.Mode=Asynchronous
PA3.Signal=USART2_RX
PA4.GPIOParameters=GPIO_Label
PA4.GPIO_Label=FCU_GPIO_H
PA4.Signal=GPIO_Input
PA5.Mode=Full_Duplex_Master
PA5.Signal=SPI1_SCK
PA6.Mode=Full_Duplex_Master
PA6.Signal=SPI1_MISO
PA7.Mode=Full_Duplex_Master
PA7.Signal=SPI1_MOSI
PA9.Mode=Activate_VBUS
PA9.Signal=USB_OTG_FS_VBUS
PB0.GPIOParameters=GPIO_Label
PB0.GPIO_Label=FCU_FCS_RUDD
PB0.Signal=S_TIM3_CH3
PB1.GPIOParameters=GPIO_Label
PB1.GPIO_Label=FCU_FCS_FLPS
PB1.Signal=S_TIM3_CH4
PB10.Mode=I2C
PB10.Signal=I2C2_SCL
PB11.Mode=I2C
PB11.Signal=I2C2_SDA
PB2.GPIOParameters=GPIO_Label
PB2.GPIO_Label=FCU_BOOT1
PB2.Signal=GPIO_Input
PB3.GPIOParameters=GPIO_Label
PB3.GPIO_Label=FCU_LED_C
PB3.Signal=GPIO_Output
PB4.GPIOParameters=GPIO_Label
PB4.GPIO_Label=FCU_LED_B
PB4.Signal=GPIO_Output
PB5.GPIOParameters=GPIO_Label
PB5.GPIO_Label=FCU_LED_A
PB5.Signal=GPIO_Output
PB6.Mode=Asynchronous
PB6.Signal=USART1_TX
PB7.Mode=Asynchronous
PB7.Signal=USART1_RX
PB8.Mode=I2C
PB8.Signal=I2C1_SCL
PB9.Mode=I2C
PB9.Signal=I2C1_SDA
PC0.GPIOParameters=GPIO_Label
PC0.GPIO_Label=FCU_GPIO_D
PC0.Signal=GPIO_Input
PC1.GPIOParameters=GPIO_Label
PC1.GPIO_Label=FCU_GPIO_C
PC1.Signal=GPIO_Output
PC10.Mode=Asynchronous
PC10.Signal=USART3_TX
PC11.Mode=Asynchronous
PC11.Signal=USART3_RX
PC12.GPIOParameters=GPIO_Label
PC12.GPIO_Label=FCU_LED_E
PC12.Signal=GPIO_Output
PC13-ANTI_TAMP.GPIOParameters=GPIO_Label
PC13-ANTI_TAMP.GPIO_Label=FCU_GPIO_G
PC13-ANTI_TAMP.Signal=GPIO_Output
PC14-OSC32_IN.GPIOParameters=GPIO_Label
PC14-OSC32_IN.GPIO_Label=FCU_GPIO_F
PC14-OSC32_IN.Signal=GPIO_Input
PC15-OSC32_OUT.GPIOParameters=GPIO_Label
PC15-OSC32_OUT.GPIO_Label=FCU_GPIO_E
PC15-OSC32_OUT.Signal=GPIO_Output
PC2.GPIOParameters=GPIO_Label
PC2.GPIO_Label=FCU_GPIO_B
PC2.Signal=GPIO_Input
PC3.GPIOParameters=GPIO_Label
PC3.GPIO_Label=FCU_GPIO_A
PC3.Signal=GPIO_Output
PC4.GPIOParameters=GPIO_Label
PC4.GPIO_Label=FCU_SPI1_CS_FLASH
PC4.Signal=GPIO_Output
PC6.GPIOParameters=GPIO_Label
PC6.GPIO_Label=FCU_FCS_AILRN
PC6.Signal=S_TIM3_CH1
PC7.GPIOParameters=GPIO_Label
PC7.GPIO_Label=FCU_FCS_ELEV
PC7.Signal=S_TIM3_CH2
PC8.GPIOParameters=GPIO_Label
PC8.GPIO_Label=FCU_ENG_PROP_2
PC8.Signal=S_TIM8_CH3
PC9.GPIOParameters=GPIO_Label
PC9.GPIO_Label=FCU_ENG_PROP_1
PC9.Signal=S_TIM8_CH4
PD2.GPIOParameters=GPIO_Label
PD2.GPIO_Label=FCU_LED_D
PD2.Signal=GPIO_Output
PH0-OSC_IN.Mode=HSE-External-Oscillator
PH0-OSC_IN.Signal=RCC_OSC_IN
PH1-OSC_OUT.Mode=HSE-External-Oscillator
PH1-OSC_OUT.Signal=RCC_OSC_OUT
RCC.HSE_VALUE=25000000
RCC.SYSCLKFreq_VALUE=25000000
RCC.SYSCLKSource=RCC_SYSCLKSOURCE_HSE
board=custom

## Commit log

2026-01-15 better folder structure, fcu schematic done, fcu peripherals done, fcu and nu stm32 projects
2026-01-15 fcu, nu schematics, problem with pins
2026-01-16 pin mess up win, starting over again
2026-01-16 added projects, schematic almost done, need revision
2026-01-16 sd card receptacle 10u capacitor
2026-01-17 version 0.1.0
2026-01-17 version 0.1.1, added dfu usb to firmware upload, changed pwm channels
2026-01-17 i forgot to change the damn label
2026-01-18 added nu i2c test point, some documentation hehe
2026-01-21 started codinggit add .
2026-01-22 firmware started, freertos, initial sensors abstractions, some pin layout changes
2026-01-22 pin refatoration, freertos code
2026-01-23 add some footprints, and pcb configs
2026-01-26 hardware: reorganizing components, im fucked
2026-01-27 hardware: initial power supply layout
2026-01-28 sensors positioned
2026-01-29 usb traces, i2c, spi, sdio, and more
2026-01-29 i2c sensors traces
2026-01-30 idk what i did here
2026-01-30 starting layout again...
2026-02-07 initial firmwares
2026-02-11 schematic and BOM done
